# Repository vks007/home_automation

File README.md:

# Home Automation
Contains source files for various Home Automation projects of mine.

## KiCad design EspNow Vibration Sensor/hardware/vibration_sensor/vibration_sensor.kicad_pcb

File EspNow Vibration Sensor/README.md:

# Piezo Vibration Sensor

Design reference for the piezo-based vibration sensor used to detect a continuously leaking tap.

The front end converts raw piezo output into a slow, smooth **envelope voltage** that an ESP8266
ADC can read directly. Detection logic (baseline tracking, thresholds, dwell) lives in firmware;
this board's job is to deliver a clean, correctly band-limited signal.

- **Supply:** single +3.3 V
- **Op-amp:** TLV9062 (dual, rail-to-rail input and output)
- **Output:** 15 mV – 1.03 V, suitable for a bare ESP-12 A0 (0–1.0 V full scale)
- **Passband:** ~194 Hz – 1.94 kHz
- **Envelope time constant:** 0.32 s

---

## Use Case

This vibration sensor will be used to detect the leakage of water inside a cistern of a toilet flush. 
This would be run on rechargeable batteries and hence should last a long time before requiring a battery recharge. This presents a few challenges as below:

- The detection circuit itself takes around 1mA while idle. This is too much for a battery which is expected to last many months. Ideally its consumption should be < 100uA.
- The leakage may be continuous or may be intermittent. If there's a small amount of leakage then water will keep seeping through and the cistern will trigger a refill every time the water goes below a certain level. When the refill happens, I expect the vibration sensor to trigger. The slow leakage may not trigger the vibration sensor - even if does, it might be difficult to differentiate it from noise.
- The circuit should be able to sleep most of the time while waking up either periodically or on activity in the vibration circuit.

---

## 1. Block diagram

```mermaid
flowchart LR
    P[Piezo element] --> A[Input protection<br/>& bias<br/>C2, R11, D1, D2, R3]
    A --> B[Band-limited gain<br/>U1A, x123<br/>194 Hz - 1.94 kHz]
    B --> C[Level re-reference<br/>VBIAS to VLOW<br/>Cc, R10]
    C --> D[Precision peak detector<br/>U1B, D3, C12<br/>tau = 0.32 s]
    D --> E[ADC scaling & filter<br/>R9a, R9b, C4]
    E --> F[ESP-12 A0]

    V1[VBIAS 1.65 V<br/>R1, R2, C10, C9] -.-> A
    V1 -.-> B
    V2[VLOW 48 mV<br/>R7, R8, C11, C13] -.-> C
    V2 -.-> D
```

### Signal chain

```
Piezo ─ C2 ─ R11 10k ─┬─ R3 100k ── VBIAS
                      ├─ D1 / D2 clamps
                      └─ U1A pin 3
                              │
                   R4 1M feedback, R5 8k2 + C7 to VBIAS    → gain 123
                              │
                    R6 8k2 ─┬─ C3 0.01µ ── VBIAS           → LPF 1.94 kHz
                            │
                            └─ Cc 0.1µ ─┬─ U1B pin 5
                                        └─ R10 100k ── VLOW (48 mV)
                              │
                    U1B pin 7 ─ D3 ─┬─ NODE X ── back to pin 6
                                    ├─ C12 10µ ── GND
                                    └─ R9a 22k ─┬─ R9b 10k ── GND
                                                ├─ C4 10µ ── GND
                                                └──► ESP-12 A0
```

**Reading the diagrams:** `┬` `├` `└` `│` are junctions — every branch hanging off one is the
same electrical node. Anything drawn hanging downward is a shunt, not part of the series path.

---

## 2. Stage functions

### Stage 1 — Input protection and bias

| Ref | Value | Role |
|---|---|---|
| C2 | 1 µF | blocks DC; couples the piezo's AC output |
| R11 | 10 k | limits fault current into the clamps and the op-amp |
| D1 | 1N5819 | clamp — anode to NODE A, cathode to +3.3 V |
| D2 | 1N5819 | clamp — anode to GND, cathode to NODE A |
| R3 | 100 k | biases NODE A to VBIAS |

A piezo is a capacitive, high-impedance source that can generate **tens to hundreds of volts**
when struck. D1 and D2 hold NODE A within one diode drop of the supply rails; R11 limits the
resulting current to a few milliamps. In normal operation both diodes are reverse-biased and
electrically invisible.

R3 sets the DC operating point at VBIAS. It also forms a high-pass with the piezo's own
capacitance (≈15 nF), rolling off below **~106 Hz** — useful rejection of structural thumps and
thermal drift, at no component cost. 100 k is chosen over a larger value to keep the resistor's
thermal noise from dominating the TLV9062's own 10 nV/√Hz.

### Stage 2 — Band-limited gain

| Ref | Value | Role |
|---|---|---|
| U1A | TLV9062 | non-inverting gain stage |
| R4 | 1 M | feedback |
| R5 | 8.2 k | gain-set leg |
| C7 | 0.1 µF | in series with R5 |
| R6 | 8.2 k | low-pass series element |
| C3 | 0.01 µF | low-pass shunt |

$$\text{AC gain} = 1 + \frac{R_4}{R_5} = 1 + \frac{1\text{M}}{8.2\text{k}} = 123$$

C7 in series with R5 is the key detail: it makes **DC gain = 1** while leaving AC gain at 123.
Without it, the op-amp's input offset voltage would be amplified 123× — up to ±220 mV of
temperature-drifting error on the output. It simultaneously sets the low end of the passband:

$$f_{HP} = \frac{1}{2\pi R_5 C_7} = \frac{1}{2\pi \cdot 8.2\text{k} \cdot 0.1\mu} \approx 194\ \text{Hz}$$

R6/C3 set the top of the passband:

$$f_{LP} = \frac{1}{2\pi R_6 C_3} = \frac{1}{2\pi \cdot 8.2\text{k} \cdot 0.01\mu} \approx 1.94\ \text{kHz}$$

**Why this band.** Turbulent flow noise from a leak is broadband hiss, typically 300 Hz – 4 kHz.
Below ~200 Hz sits everything that should be rejected: mains hum, footsteps, door slams, HVAC,
and piezo thermal drift. The passband is deliberately placed to keep the former and discard the
latter.

Only one gain stage is used. Required gain-bandwidth is 123 × 2 kHz ≈ 250 kHz against the
TLV9062's 10 MHz, so a single stage is comfortable — which frees the second op-amp for Stage 4.

### Stage 3 — Level re-referencing

| Ref | Value | Role |
|---|---|---|
| Cc | 0.1 µF | AC-couples the signal off VBIAS |
| R10 | 100 k | biases U1B's +IN to VLOW |

Stages 1–2 operate around VBIAS = 1.65 V. The bare ESP-12 ADC accepts **0–1.0 V**, so the
detector must not rest at 1.65 V. Cc strips the VBIAS reference and R10 re-establishes the
signal around **VLOW ≈ 48 mV**, close to ground.

$$f_c = \frac{1}{2\pi R_{10} C_c} = \frac{1}{2\pi \cdot 100\text{k} \cdot 0.1\mu} \approx 16\ \text{Hz}$$

16 Hz is far below the 194 Hz passband, so this coupling has no effect on the signal of
interest. R10's 100 k is what places the corner there — feeding Cc into the stiff VLOW divider
directly would put it near 1 kHz and eat the passband.

⚠️ **Cc must be film or ceramic, not electrolytic.** It sits between a 1.65 V node and a 48 mV
node, so an electrolytic would be reverse-biased.

### Stage 4 — Precision peak detector (envelope)

| Ref | Value | Role |
|---|---|---|
| U1B | TLV9062 | superdiode buffer |
| D3 | 1N5819 | rectifier, **inside** the feedback loop |
| C12 | 10 µF | envelope storage (+ to NODE X, − to GND) |

D3 sits inside U1B's feedback loop — the feedback wire is taken from **NODE X (the cathode)**,
not from pin 7. This divides the diode's forward drop by the op-amp's open-loop gain, reducing
it to microvolts. A passive rectifier would instead have a ~0.2 V dead zone that drifts at
−2 mV/°C, making small signals invisible and the detection threshold temperature-dependent.

The storage network returns to **GND**, not VBIAS, which is what places the resting output near
48 mV instead of 1.65 V.

$$\tau = (R_{9a} + R_{9b}) \times C_{12} = 32\text{k} \times 10\mu \approx 0.32\ \text{s}$$

Fast attack, slow decay: the envelope rises quickly on vibration and rides through the gaps in
the hiss rather than following individual cycles.

The TLV9062's rail-to-rail input **and** output range is what allows this stage to operate
within 50 mV of the negative rail. A non-RRIO op-amp would not work here.

### Stage 5 — ADC scaling and filtering

| Ref | Value | Role |
|---|---|---|
| R9a | 22 k | divider top / discharge path |
| R9b | 10 k | divider bottom / discharge path |
| C4 | 10 µF | ADC anti-alias and noise filter |

The two-resistor divider does three jobs at once, which is why no output buffer is needed:

1. **Scales** the envelope into the ESP-12's 0–1.0 V window
2. **Discharges** C12, setting the 0.32 s time constant
3. **Drops the source impedance** to 6.9 k, low enough for the SAR ADC's sampling capacitor

| | Value |
|---|---|
| Divider ratio | 10 k / 32 k = 0.3125 |
| Rest voltage at A0 | 48 mV × 0.3125 ≈ **15 mV** (~15 counts) |
| A0 at full op-amp swing (3.3 V) | ≈ **1.03 V** |
| Source impedance | 22 k ∥ 10 k ≈ **6.9 k** |

**A0 cannot exceed ~1.03 V even if U1B saturates against the rail.** The divider is inherently
protective, so no clamp diode is required on the ADC input.

C4 sets the final noise filter:

$$f_c = \frac{1}{2\pi \cdot 6.9\text{k} \cdot 10\mu} \approx 2.3\ \text{Hz}$$

The envelope carries information at roughly 0.5 Hz, so 2.3 Hz preserves the signal completely
while heavily attenuating everything above it. This matters on ESP8266: the radio draws
250–350 mA in millisecond bursts, and its ADC shares silicon with the RF section. This capacitor
is what makes ESP-side readings as clean as a quiet, radio-free microcontroller's.

C4 is polarised — **+ to the A0 node, − to GND**.

### References and decoupling

| Ref | Value | Role |
|---|---|---|
| R1, R2 | 100 k | VBIAS divider → 1.65 V |
| C10 | 10 µF | VBIAS bulk |
| C9 | 0.1 µF | VBIAS high-frequency |
| R7 | 100 k | VLOW divider top |
| R8 | 1.5 k | VLOW divider bottom |
| C11 | 10 µF | VLOW bulk |
| C13 | 0.1 µF | VLOW high-frequency |
| U1C | — | TLV9062 power unit |
| C8 | 0.1 µF | op-amp supply decoupling |

$$V_{BIAS} = 3.3 \times \frac{100\text{k}}{200\text{k}} = 1.65\ \text{V}
\qquad
V_{LOW} = 3.3 \times \frac{1.5\text{k}}{101.5\text{k}} \approx 48\ \text{mV}$$

Each rail carries both a 10 µF bulk capacitor and a 0.1 µF ceramic: electrolytics have poor
high-frequency impedance, and VBIAS ripple is amplified by the ×123 stage.

⚠️ **C8 must be placed physically adjacent to pins 8 and 4.** A 10 MHz op-amp with a 1 M
feedback resistor can oscillate without local decoupling, and the capacitor's value is
irrelevant if it sits 30 mm away.

---

## 3. Complete bill of materials

| Ref | Value | Notes |
|---|---|---|
| U1 | TLV9062 | dual RRIO op-amp, SOIC-8 |
| Piezo1 | — | piezo disc |
| C2 | 1 µF | film preferred (+ toward R11 if polarised) |
| C3 | 0.01 µF | |
| C4 | 10 µF | + to A0 node |
| C7 | 0.1 µF | |
| C8 | 0.1 µF | at op-amp pins 8 / 4 |
| C9 | 0.1 µF | |
| C10 | 10 µF | + to VBIAS |
| C11 | 10 µF | + to VLOW |
| C12 | 10 µF | + to NODE X |
| C13 | 0.1 µF | |
| Cc | 0.1 µF | **film or ceramic only** |
| D1, D2 | 1N5819 | input clamps |
| D3 | 1N5819 | rectifier, inside feedback loop |
| R1, R2 | 100 k | |
| R3 | 100 k | |
| R4 | 1 M | feedback |
| R5 | 8.2 k | gain leg |
| R6 | 8.2 k | |
| R7 | 100 k | |
| R8 | 1.5 k | |
| R9a | 22 k | |
| R9b | 10 k | |
| R10 | 100 k | |
| R11 | 10 k | |

### Key parameters

| Parameter | Value |
|---|---|
| Gain (AC) | 123 |
| Gain (DC) | 1 |
| Passband | 194 Hz – 1.94 kHz |
| VBIAS | 1.65 V |
| VLOW | 48 mV |
| Envelope τ | 0.32 s |
| ADC filter corner | 2.3 Hz |
| Output at rest | ~15 mV (~15 counts) |
| Output maximum | ~1.03 V |

---

## 4. Bring-up

A0 should read **~15 counts at rest**, rising with vibration.

| Reading | Likely cause |
|---|---|
| Pinned at 1023 | C12 or the divider returns to VBIAS instead of GND |
| Stuck at 0 | Cc open, R10 missing, or D3 reversed |
| ~500 at rest | VLOW divider wrong — check for 15 k fitted instead of 1.5 k |
| Everything at 0 V | VBIAS rail shorted to GND |

### Gain adjustment

At ×123 the op-amp reaches the rail at roughly **27 mV peak** from the piezo, so sharp
transients clip. This is acceptable for an event detector, and clipped transients are rejected
by the firmware's dwell logic. If the ambient floor sits too high, reduce R4:

| R4 | Gain |
|---|---|
| 1 M | 123 |
| 470 k | 58 |
| 220 k | 28 |

---

## 5. Testing on a D1 Mini

The D1 Mini's A0 has an onboard 220 k / 100 k divider giving a **0–3.3 V** range, rather than
the bare ESP-12's 0–1.0 V. To use the full ADC range, move a single wire:

| | ESP-12 | D1 Mini |
|---|---|---|
| A0 tap point | R9a / R9b junction | **NODE X** (D3 cathode / C12 top) |
| Everything else | — | identical |

Leave R9a and R9b fitted — they remain C12's discharge path, so τ stays 0.32 s. When tapping
NODE X, place C4 directly between the **A0 pin and GND** with short leads.

NODE X swings 48 mV – 3.3 V, matching the D1 Mini's range. The 32 k source impedance into its
~320 k input costs about 9% attenuation — constant and linear, and absorbed by the firmware's
adaptive baseline.

### Breadboard note

This circuit contains 1 M and 100 k nodes sitting near a 2.4 GHz transmitter. On a breadboard
these pick up mains hum and RF, so the noise floor will look worse than on the final board.
**Do not set detection thresholds from breadboard traces.** Use a star ground back to a single
point at the ESP's GND pin, and keep the piezo leads and U1A's feedback loop short.

---

## 6. Firmware interface

The board presents a slow, smooth envelope voltage on A0. Firmware still needs to decide what it
means, because the *ambient* hiss level drifts with time of day, appliances, and neighbouring
plumbing. The intended chain is:

1. Sample A0 at a fixed interval
2. Track an **adaptive baseline** (EWMA, frozen while an event is active)
3. Compute a **z-score** against running dispersion
4. Apply **hysteresis and a dwell timer** so only sustained vibration registers as a leak

A leaking tap produces *continuous* hiss; impacts and handling produce *transients*. That
difference lives in the envelope's persistence, which is why dwell time — not peak amplitude —
is the primary discriminator.

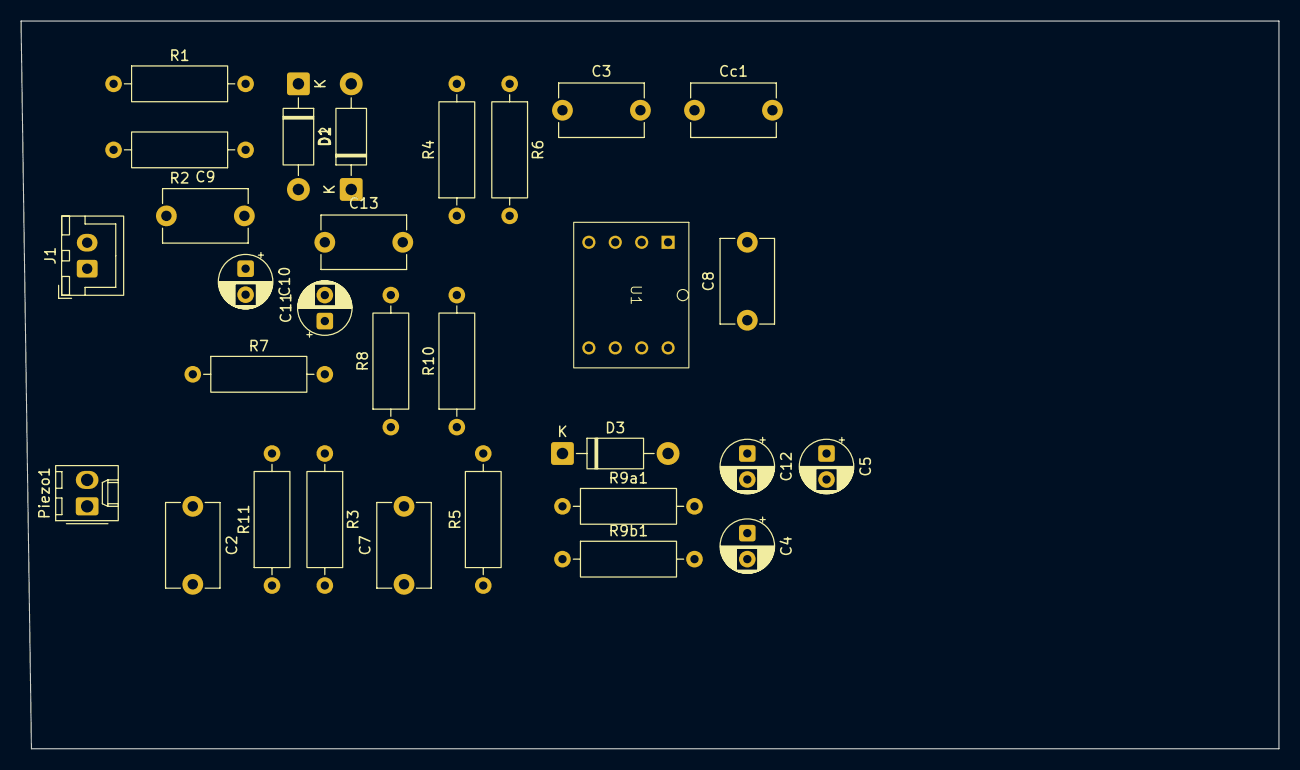
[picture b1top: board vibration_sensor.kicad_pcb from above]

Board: 2 copper layers, 121.0 x 70.0 mm, 30 parts (0 on the bottom side), 15 nets, no tracks yet.

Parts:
C2, C7, C8, C9, C13: 0.1u; C_Disc_D8.0mm_W5.0mm_P7.50mm
C3: 0.01u; C_Disc_D8.0mm_W5.0mm_P7.50mm
C4, C10, C11: 1u; CP_Radial_D5.0mm_P2.50mm
C5, C12: 10u; CP_Radial_D5.0mm_P2.50mm
Cc1: 0.1u; C_Disc_D8.0mm_W5.0mm_P7.50mm
D1, D2, D3: 1N5819; D_DO-41_SOD81_P10.16mm_Horizontal
J1: Conn_01x02_Pin; JST_XH_B2B-XH-A_1x02_P2.50mm_Vertical
Piezo1: Molex_KK-254_AE-6410-02A_1x02_P2.54mm_Vertical
R1, R2, R3, R7, R10: 100K; R_Axial_DIN0309_L9.0mm_D3.2mm_P12.70mm_Horizontal
R4: 1M; R_Axial_DIN0309_L9.0mm_D3.2mm_P12.70mm_Horizontal
R5, R6: 8K2; R_Axial_DIN0309_L9.0mm_D3.2mm_P12.70mm_Horizontal
R8: 1K5; R_Axial_DIN0309_L9.0mm_D3.2mm_P12.70mm_Horizontal
R9a1: 22K; R_Axial_DIN0309_L9.0mm_D3.2mm_P12.70mm_Horizontal
R9b1, R11: 10K; R_Axial_DIN0309_L9.0mm_D3.2mm_P12.70mm_Horizontal
U1: TLV9062; tl9062_dip

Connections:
+3.3V: C8.2, D1.1 (K), J1.2, R1.1, R7.1, U1.8 (V+)
/PIEZO_A: C2.1, Piezo1.1 (Pin1)
/To Bare ESP ADC (0-1V): C4.1, R9a1.2, R9b1.1
/To D1 Mini ADC (0-3V): C5.1, C12.1, D3.1 (K), R9a1.1, U1.6 (-)
/VBIAS: C3.1, C7.1, C9.2, C10.1, R1.2, R2.1, R3.2
/VLOW: C11.1, C13.2, R7.2, R8.1, R10.1
GND: C4.2, C5.2, C8.1, C9.1, C10.2, C11.2, C12.2, C13.1, D2.2 (A), J1.1, Piezo1.2 (Pin2), R2.2, R8.2, R9b1.2, U1.4 (V-)
unnamed: C2.2, R11.1
unnamed: C3.2, Cc1.1, R6.2
unnamed: C7.2, R5.2
unnamed: D1.2 (A), D2.1 (K), R3.1, R11.2, U1.3 (+)
unnamed: D3.2 (A), U1.7
unnamed: R4.2, R6.1, U1.1
unnamed: R4.1, R5.1, U1.2 (-)
unnamed: Cc1.2, R10.2, U1.5 (+)

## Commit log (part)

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2019-01-06 Initial version of Door sensor - fully working version with Home Assistant.
2019-03-03 KBR Tasmota config file v 5.14
2019-03-03 Included json to publish state of the sensor. Removed detailed mqtt topic names from config.json
2019-03-03 Initial commit for wireless water controller. This is still experimental, not fully working version yet
2019-06-30 Added config backups of Tasmota devices
2019-06-30 replaced this folder with config_backup
2019-06-30 new circuit which I would like to build in future
2019-08-13 Intial version - working fully except for the junk characters between communication between ATTiny & ESP
2019-08-17 interim checkin - I2C working well Curtain logic not working yet.
2019-08-19 changed code to work with pins PB3/PB4 for the encoder. tested - all working
2019-08-20 Fully working version with new I2C based ATTiny encoder
2019-08-26 implemented status LED - working implemented auto stop when curtain reaches the top based on hall sensor - but this is not working yet.
2019-08-28 - shifted secrets to libraries folder - shifted DebugUtils to libraries folder - fixed all PIN nos according to hardware.
    Fully working version of the curtain with auto stop working too - although hardware for auto stop needs improvement
2019-09-08 changed MQTT server to be hassio.local than the IP. Started publishing IP in the message.
2019-09-08 changed from hardcoded MQTT IP to dns name
2020-01-13 initial file
2020-02-08 firmware file for tank controller, fully working version compiled with ESPHome 1.14.3 & HA version 0.103.6
2020-02-15 changed from hassio.local to IP address for MQTT
2020-02-23 initial commit. project for general esp 32 cam
2020-02-23 initial commit. project for motion detect esp32 cam
2020-03-12 removed OTA code as that wasnt working
2020-03-22 replaced use of async MQTT library with pubsub library for stability and speed of camera
2020-06-07 updated to do list
2020-07-08 renamed config_backup to tasmota
2020-07-08 checkin to renamed folder - tasmota
2020-07-08 Revert "checkin to renamed folder - tasmota"
    This reverts commit 4b9111cbc920184c25a1780e0e6fabd869fd3db7.
2020-07-08 initial checkin of tasmota files. ver no of tasmota for files are: Config_Overhead_Tank -6.5.0.12 Config_Temple_Light - 6.3.0.17 Config_Parking_Light - 6.5.0 KBR_config_backup - 6.5.0.12
2020-07-08 changed TelePeriod to 60 sec tasmota ver 6.5.0.12
2020-07-08 Ver 2.0 , removed config , WiFimanager, introduced header define based config
2020-07-08 example secrets file
2020-07-19 minor comment change
2020-07-19 added IP & MAC sensors
2020-08-09 initial version - fully working
2020-08-09 many changes, stable working version. this does not have sleep functionality
2020-08-09 included version info
2020-08-16 shifted all include files from sketches/libraries/myfiles folder to this folder from now on. include dummy includes in the original location
2020-08-16 initial checkin
2021-03-21 various changes
2021-05-30 included support for ESP12, made code generic
2021-05-30 Schematic for ESP12 module
2021-06-05 lots of changes, interim checkin, not working still
2021-06-05 fixed sleep crash issue, all working code. have to fix published values yet. interim checkin
2021-06-05 fixed decimal places for flow and total volume
2021-06-05 fully working code, all issues fixed.
2021-06-06 including hash defines
2021-06-06 included RTCmillis
2021-06-09 removed timer, changed config params
2021-06-09 image files
2021-06-10 moving to platformio from arduino IDE
2021-06-10 initial checkin after moving from Arduino to Platformio
2021-06-11 separate timers for update/publish
2021-06-13 implemented critical section for pulses
2021-07-05 parking, temple - initial checkin. tank config - updated with 2 switches
2021-11-02 moved ip address to separate topic, moved some settings to DoorConfig.h
2021-11-02 changed names of defines to be inline with home assistant secrets file
2021-11-02 corrected json formatting mistake
2021-12-30 initial files
2021-12-30 changed to new struct as in ESP8266Gateway
2021-12-31 added health check
2022-01-08 added more entries
2022-01-08 added fn , commented a few others. will solve them later
2022-01-09 initial commit for esp8266 gateway
2022-01-09 added more values
2022-01-09 initial add - espnow temperature node
2022-01-29 working version with RTC memory for wifi channel
2022-01-29 added RTC mem functions
2022-02-08 checkin working code without serial comm bw AT-ESP
2022-02-12 Fully working version of espnow based door sensor
2022-02-12 changed to defining DEBUG as 0 and 1
2022-02-12 changed from RTC mem to eeprom for storing channel info
2022-02-12 confimred to new way to specify debug
2022-02-14 turned debug ON and turned security OFF
2022-02-14 minor changes on config
2022-02-15 stability changes for WiFi, other minor changes
2022-02-16 minor change
2022-02-16 uncommented map_generic , it is likely to break esp32 compilation
2022-02-16 included message rate
2022-02-16 refactored code, introduced testing mode
2022-02-16 lot of changes
2022-02-18 interim checkin, current code is failing after connection to MQTT once, it doesnt connect again
2022-02-19 uses async mqtt client library - the MQTT connection is not working with this, interim checkin to save code.
2022-02-19 added util functions and == operator
2022-02-19 schematic for door sensor and motion sensor
2022-02-20 added one more env balconydoor12e
2022-02-22 corrected the diagram
2022-02-24 moved library to default env
2022-03-12 minor changes
2022-03-13 addes static ip file
2022-03-31 made logic to cut/retain power configurable and other minor changes
2022-05-14 moved logic to loop, removed batt voltage logic
2022-05-14 changed ssid
2022-05-14 disabled health check posting of msg
2022-05-22 updated circuit and ATtiny code to stop sending signal to ESP
2022-05-22 initial
2022-05-25 fixed AP_STA issue + fixed publish of startup msg
2022-05-25 changed back to GF gateway, other minor changes
2022-06-11 LOGIC_NORMAL, main door-> FF gateway
2022-06-11 many changes in gateway
2022-06-12 made esputil a class , major changes
2022-06-12 code migrated to esputil class
2022-06-12 minot changes, +channel publishing on gateway
2022-07-10 routine
2022-07-10 ezLED changes
2022-07-10 included PIR sensor, other espnow changes
2022-07-12 fixed bug with key==nullptr, moved config entries
2022-07-12 moved entries to config.h
2022-07-23 ESP32 touch module , initial checkin
2022-07-23 shifted macros to this file
2022-07-23 included staus LED
2022-07-28 misc files
2022-07-28 gitignore
2022-07-30 intermin checkin - passing MAC to ESP working fine
2022-07-31 espnow OTA changes
2022-09-04 espnow struc changes
2022-10-29 fixed deepsleep issue
2022-10-29 added schematic and project photo
2022-11-08 added
2022-12-21 solved MQTT max len bug in gateway and included OTA capability to espnpow Door sensor
2022-12-21 added MAC
2023-01-08 initial files for sonoff POW R2
2023-01-16 included mapping of buttons with touch pad
2023-01-16 included HARestAPI library
2023-01-21 interim check in
2023-01-28 interim checkin
2023-01-28 changed signature of initializeESP method
2023-01-29 version 1 of ESPnow water sensor and controller - all working
2023-01-29 make espController changes compatible to ESP32
2023-02-01 implemented conditions to monitor connection to sensor
2023-02-04 V2 , all working and installed in W8 for trials.
2023-02-04 changed method names and signatures
2023-02-04 included OTA
2023-02-11 fixed sumpLED bug
2023-02-11 added signal graph and tank led
2023-02-12 removed start/stop functionality, refactored code
2023-02-19 added test sensor
2023-02-25 removed usage of wifi and changed default channel.
2023-06-25 many changes
2023-07-18 added SF gateway and other minor changes
2023-07-18 fixed bugs
2023-07-18 regular checkin
2023-10-23 docker stack files for media server
2023-10-23 hello world
2023-10-23 remove files
2023-10-23 deleted hello world
2024-12-07 minor changes across files
2024-12-29 initial & interim checkin
2025-01-12 documented a MQTT bug and enhanced message length handling capability
2025-01-19 changed code to suite new build of sensor
2025-01-19 put in doxygen style comments
2025-01-19 included instantrestart + document tags
2025-01-19 made code modular
2025-01-19 added webpage to show processed messages
2025-01-25 wrote readme
2025-01-25 removed sonoff2ch files , added them in projects
